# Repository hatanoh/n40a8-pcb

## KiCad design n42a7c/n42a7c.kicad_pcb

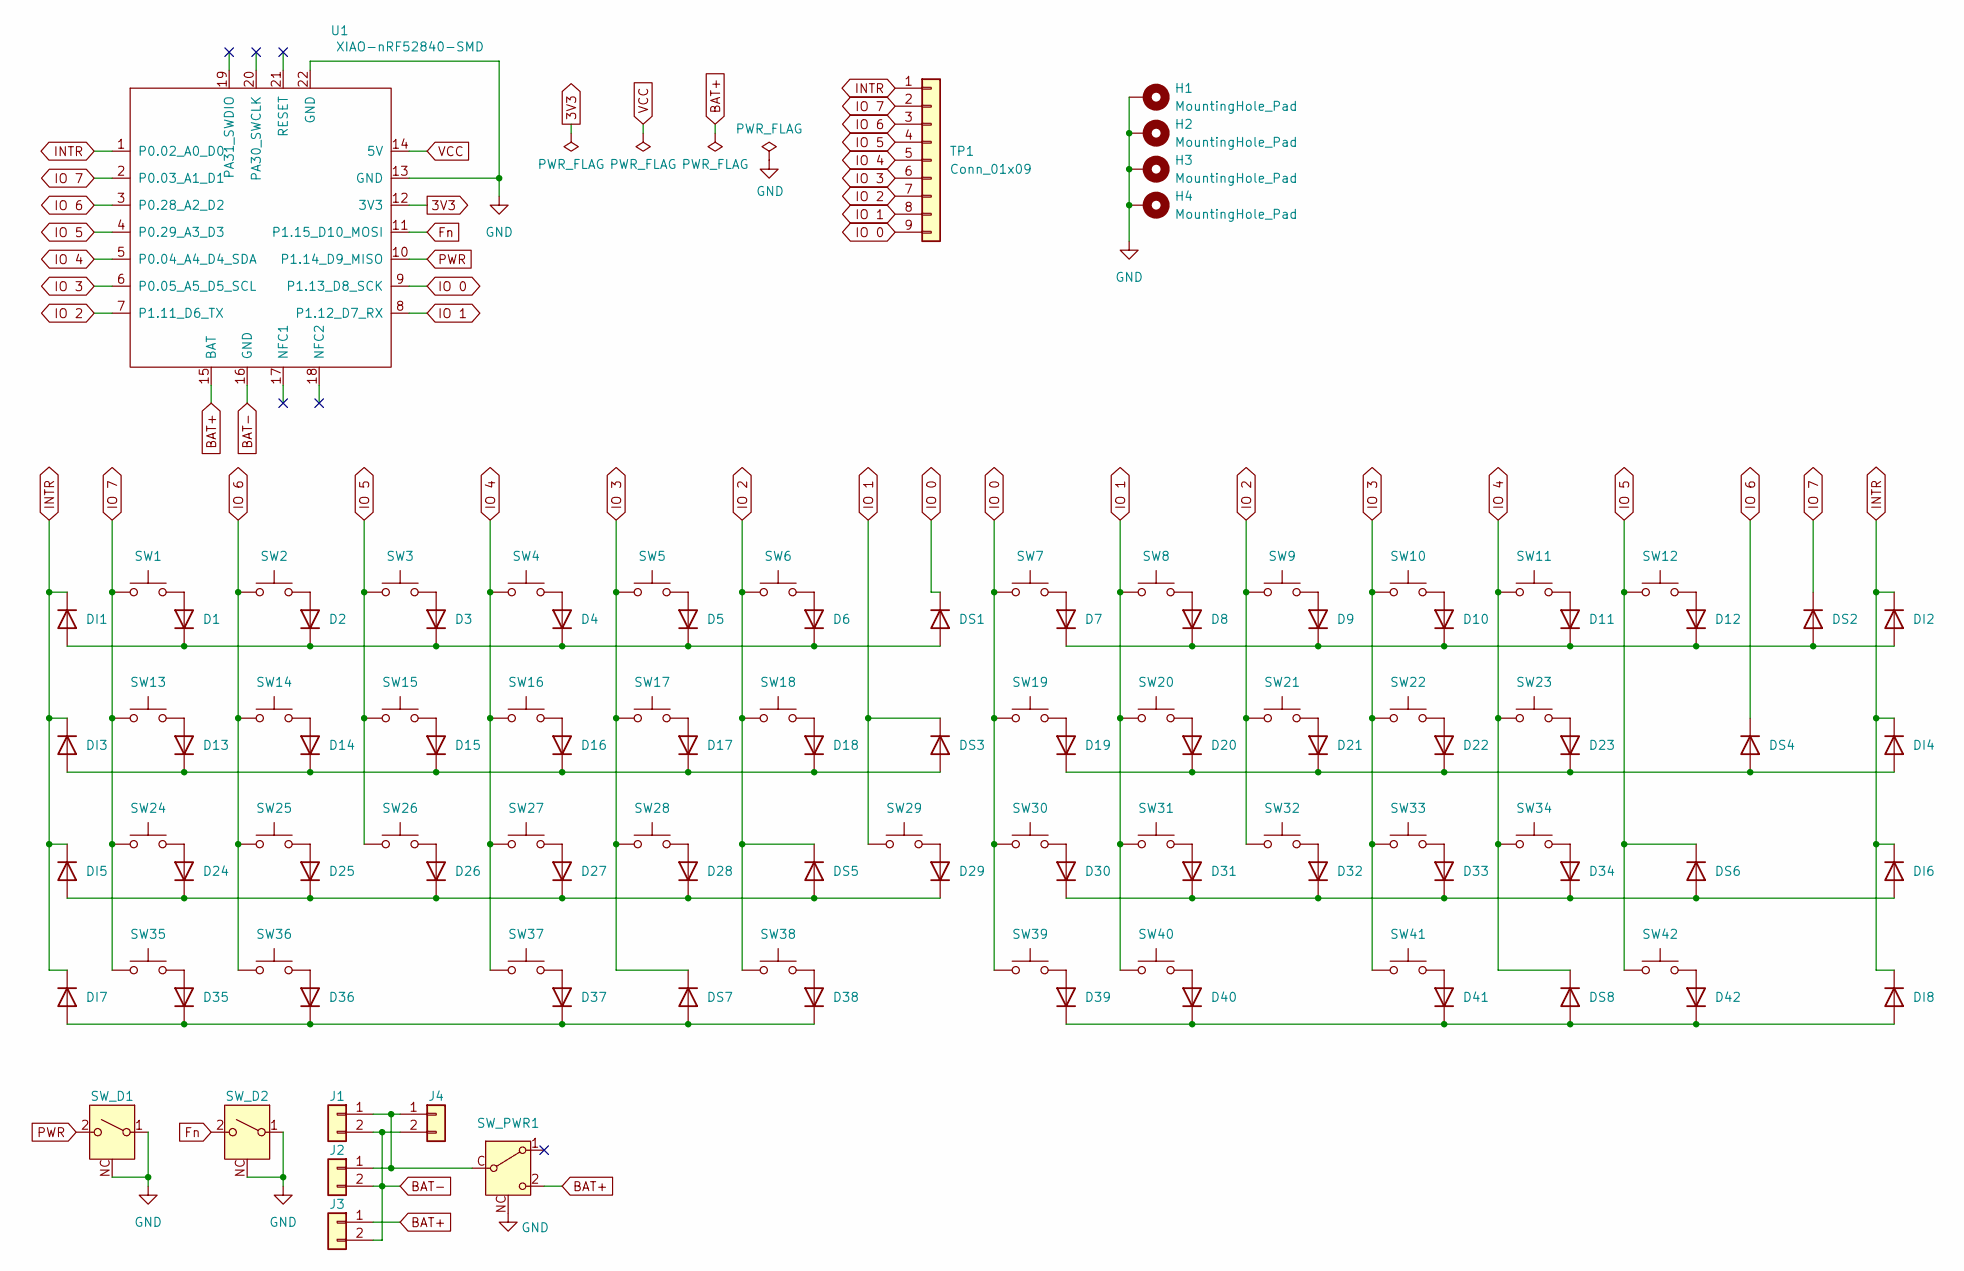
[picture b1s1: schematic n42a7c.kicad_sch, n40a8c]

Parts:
D1, D2, D3, D4, D5, D6, D7, D8, D9, D10, D11, D12, D13, D14, D15, D16, D17, D18, D19, D20, D21, D22, D23, D24, D25, D26, D27, D28, D29, D30, D31, D32, D33, D34, D35, D36, D37, D38, D39, D40, D41, D42: 1N4148W; D_SOD-123
DI1, DI2, DI3, DI4, DI5, DI6, DI7, DI8: 1N4148W; D_SOD-123
DS1, DS2, DS3, DS4, DS5, DS6, DS7, DS8: 1N4148W; D_SOD-123
H1, H2, H3, H4: MountingHole_Pad; MountingHole_M3_plating_truss
J1: S2B-PH-SM4-TB; JST_PH_S2B-PH-SM4-TB_1x02-1MP_P2.00mm_Horizontal
J2, J3: PinHeader_1x02_P2.00mm_Vertical
J4: S2B-PH-K; JST_PH_S2B-PH-K_1x02_P2.00mm_Horizontal
SW1, SW12: CPG151101S11-16; CPG151101S11_1.5u
SW2, SW3, SW4, SW5, SW6, SW7, SW8, SW9, SW10, SW11, SW14, SW15, SW16, SW17, SW18, SW19, SW20, SW21, SW22, SW25, SW26, SW27, SW28, SW29, SW30, SW31, SW32, SW33: CPG151101S11-16; CPG151101S11_1u
SW13, SW34: CPG151101S11-16; CPG151101S11_1.75u
SW23, SW24, SW39: CPG151101S11-16; CPG151101S11_2.25u
SW35, SW36, SW37, SW40, SW41, SW42: CPG151101S11-16; CPG151101S11_1.25u
SW38: CPG151101S11-16; CPG151101S11_2u
SW_D1, SW_D2: SKTDLDE010
SW_PWR1: SSSS811101
TP1: Conn_01x09; PinHeader_1x09_P1.27mm_Conthrough
U1: XIAO-nRF52840-SMD; XIAO-nRF52840-DIP2

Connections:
3V3: U1.12 (3V3)
BAT+: J3.1, SW_PWR1.2 (C), U1.15 (BAT)
BAT-: J1.2, J2.2, J3.2, J4.2, U1.16 (GND)
Fn: SW_D2.2 (B), U1.11 (P1.15_D10_MOSI)
GND: H1.1, H2.1, H3.1, H4.1, SW_D1.1 (A), SW_D1.NC, SW_D2.1 (A), SW_D2.NC, SW_PWR1.NC, U1.13 (GND), U1.22 (GND)
INTR: DI1.1 (K), DI2.1 (K), DI3.1 (K), DI4.1 (K), DI5.1 (K), DI6.1 (K), DI7.1 (K), DI8.1 (K), TP1.1, U1.1 (P0.02_A0_D0)
IO 0: DS1.1 (K), SW7.1, SW19.1, SW30.1, SW39.1, TP1.9, U1.9 (P1.13_D8_SCK)
IO 1: DS3.1 (K), SW8.1, SW20.1, SW29.1, SW31.1, SW40.1, TP1.8, U1.8 (P1.12_D7_RX)
IO 2: DS5.1 (K), SW6.1, SW9.1, SW18.1, SW21.1, SW32.1, SW38.1, TP1.7, U1.7 (P1.11_D6_TX)
IO 3: DS7.1 (K), SW5.1, SW10.1, SW17.1, SW22.1, SW28.1, SW33.1, SW41.1, TP1.6, U1.6 (P0.05_A5_D5_SCL)
IO 4: DS8.1 (K), SW4.1, SW11.1, SW16.1, SW23.1, SW27.1, SW34.1, SW37.1, TP1.5, U1.5 (P0.04_A4_D4_SDA)
IO 5: DS6.1 (K), SW3.1, SW12.1, SW15.1, SW26.1, SW42.1, TP1.4, U1.4 (P0.29_A3_D3)
IO 6: DS4.1 (K), SW2.1, SW14.1, SW25.1, SW36.1, TP1.3, U1.3 (P0.28_A2_D2)
IO 7: DS2.1 (K), SW1.1, SW13.1, SW24.1, SW35.1, TP1.2, U1.2 (P0.03_A1_D1)
unnamed: D1.2 (A), SW1.2
unnamed: D1.1 (K), D2.1 (K), D3.1 (K), D4.1 (K), D5.1 (K), D6.1 (K), DI1.2 (A), DS1.2 (A)
unnamed: D2.2 (A), SW2.2
unnamed: D3.2 (A), SW3.2
unnamed: D4.2 (A), SW4.2
unnamed: D5.2 (A), SW5.2
unnamed: D6.2 (A), SW6.2
unnamed: D7.2 (A), SW7.2
unnamed: D8.2 (A), SW8.2
unnamed: D9.2 (A), SW9.2
unnamed: D10.2 (A), SW10.2
unnamed: D7.1 (K), D8.1 (K), D9.1 (K), D10.1 (K), D11.1 (K), D12.1 (K), DI2.2 (A), DS2.2 (A)
unnamed: D11.2 (A), SW11.2
unnamed: D12.2 (A), SW12.2
unnamed: D13.2 (A), SW13.2
unnamed: D13.1 (K), D14.1 (K), D15.1 (K), D16.1 (K), D17.1 (K), D18.1 (K), DI3.2 (A), DS3.2 (A)
unnamed: D14.2 (A), SW14.2
unnamed: D15.2 (A), SW15.2
unnamed: D16.2 (A), SW16.2
unnamed: D17.2 (A), SW17.2
unnamed: D18.2 (A), SW18.2
unnamed: D19.2 (A), SW19.2
unnamed: D19.1 (K), D20.1 (K), D21.1 (K), D22.1 (K), D23.1 (K), DI4.2 (A), DS4.2 (A)
unnamed: D20.2 (A), SW20.2
unnamed: D21.2 (A), SW21.2
unnamed: D22.2 (A), SW22.2
unnamed: D23.2 (A), SW23.2
unnamed: D24.2 (A), SW24.2
unnamed: D24.1 (K), D25.1 (K), D26.1 (K), D27.1 (K), D28.1 (K), D29.1 (K), DI5.2 (A), DS5.2 (A)
unnamed: D25.2 (A), SW25.2
unnamed: D26.2 (A), SW26.2
unnamed: D27.2 (A), SW27.2
unnamed: D28.2 (A), SW28.2
unnamed: D29.2 (A), SW29.2
unnamed: D30.2 (A), SW30.2
unnamed: D30.1 (K), D31.1 (K), D32.1 (K), D33.1 (K), D34.1 (K), DI6.2 (A), DS6.2 (A)
unnamed: D31.2 (A), SW31.2
unnamed: D32.2 (A), SW32.2
unnamed: D33.2 (A), SW33.2
unnamed: D34.2 (A), SW34.2
unnamed: D35.2 (A), SW35.2
unnamed: D35.1 (K), D36.1 (K), D37.1 (K), D38.1 (K), DI7.2 (A), DS7.2 (A)
unnamed: D36.2 (A), SW36.2
unnamed: D37.2 (A), SW37.2
unnamed: D38.2 (A), SW38.2
unnamed: D39.2 (A), SW39.2
unnamed: D39.1 (K), D40.1 (K), D41.1 (K), D42.1 (K), DI8.2 (A), DS8.2 (A)
unnamed: D40.2 (A), SW40.2
unnamed: D41.2 (A), SW41.2
unnamed: D42.2 (A), SW42.2
unnamed: J1.1, J2.1, J4.1, SW_PWR1.C (B)
PWR: SW_D1.2 (B), U1.10 (P1.14_D9_MISO)
VCC: U1.14 (5V)

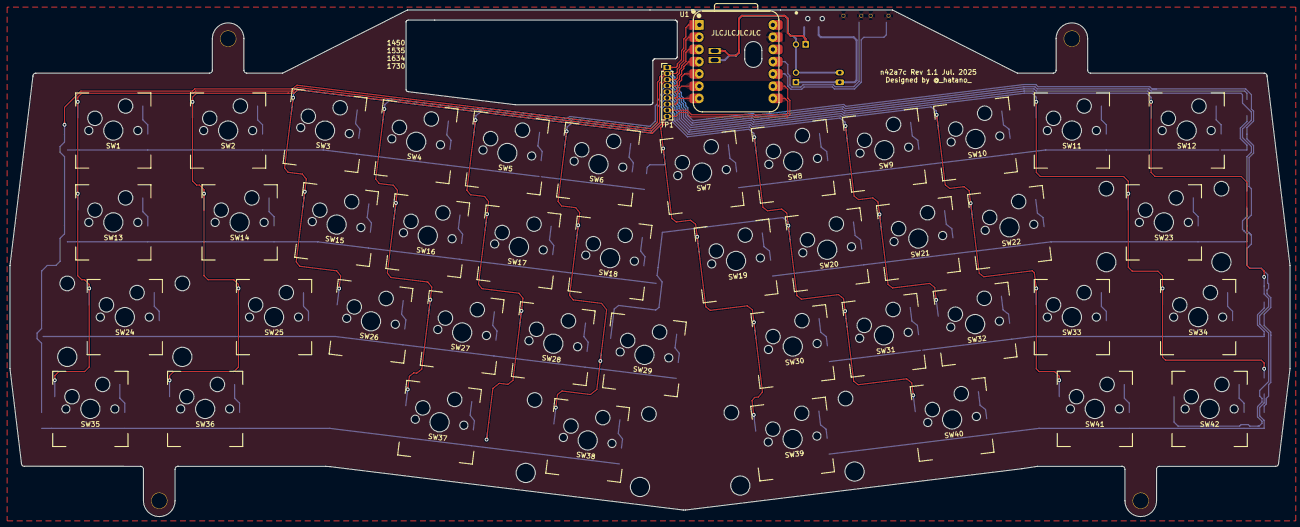
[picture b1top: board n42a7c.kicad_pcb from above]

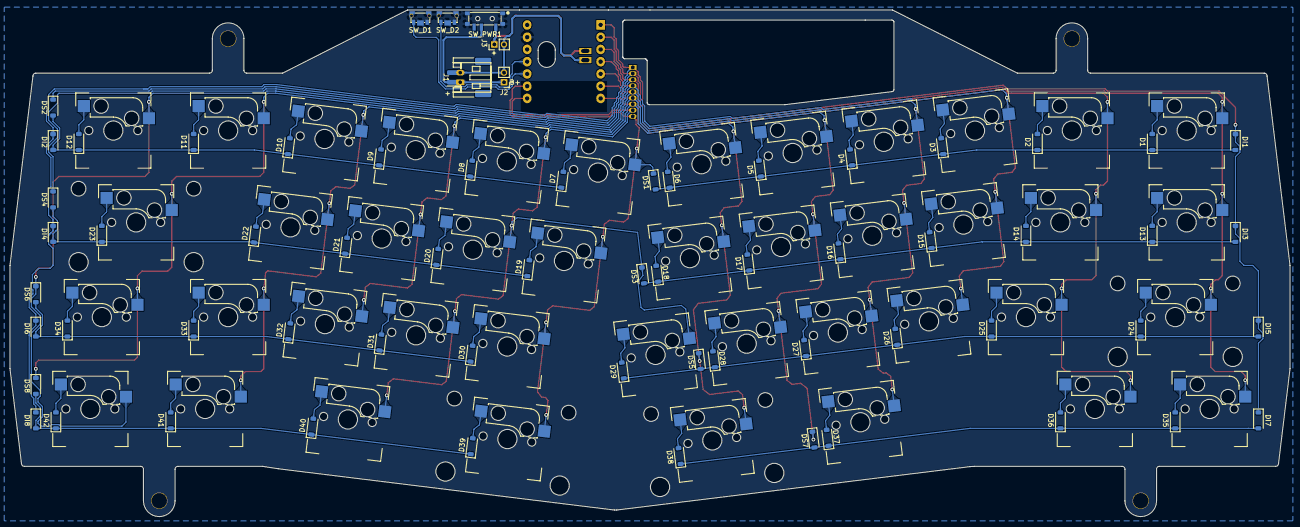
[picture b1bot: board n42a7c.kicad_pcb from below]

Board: 2 copper layers, 265.5 x 105.1 mm, 113 parts (107 on the bottom side), 65 nets.

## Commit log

2025-05-08 Initial commit.
2025-05-08 add submodule https://github.com/Seeed-Studio/OPL_Kicad_Library.git
2025-05-08 revise wiring
2025-05-08 cosmetic change
2025-05-22 M2→M2.6
2025-05-26 update clearance (for truss)
2025-05-26 M2.6→M3
2025-06-05 revice tab
2025-06-06 revise tab
2025-06-06 create production data
2025-06-06 comply design rule (JLCPCB)
2025-06-08 revise keysocket footprint. revise production pcb data.
2025-06-08 add n42a7c valiant.
2025-06-09 revise n42a7c
2025-06-10 add production files
2025-06-11 revise SSAJ1x0100 footprint / symbol
2025-06-11 remove work
2025-06-12 revise power switch
2025-06-16 revise switch pos.
2025-06-16 revise power connector
2025-06-17 revise power SW
2025-06-19 revise switch
2025-06-20 revise switch symbol/footprint
2025-06-21 create plate
2025-06-21 revise edge.cut
2025-06-24 revise power line
2025-06-24 add document
2025-06-25 revise sw
2025-06-26 revise 3dmodel path
2025-06-26 revise 3dshape path
2025-06-30 correct foots
2025-06-30 create plate / production PCB
2025-06-30 revise power conn
2025-06-30 remove n40a8c
2025-07-01 revise keylayout
2025-07-02 create plate/production PCB
2025-07-02 revise
2025-07-02 create production plate
2025-07-06 revise wire
2025-07-18 regen production pcb data
